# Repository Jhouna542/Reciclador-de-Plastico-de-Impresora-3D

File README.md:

# Reciclador-de-Plastico-de-Impresora-3D
El repositorio contiene los esquemas y PCB en KiCad, el código del microcontrolador ATxmega128A1U junto con su esqueleto y el informe del proyecto en formato PDF y en formato IEEE.

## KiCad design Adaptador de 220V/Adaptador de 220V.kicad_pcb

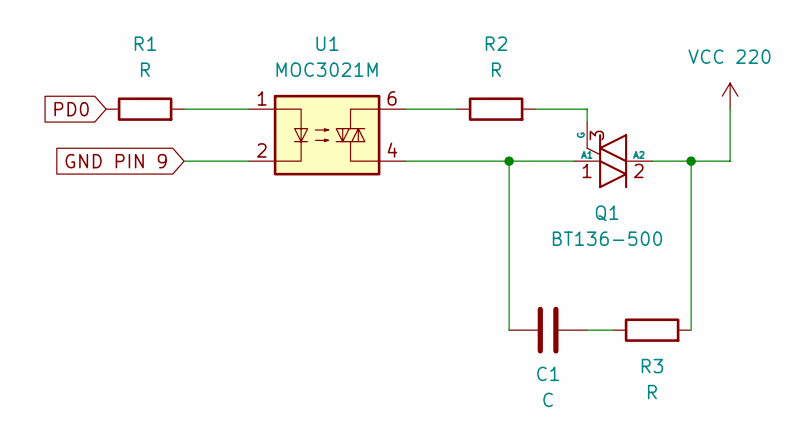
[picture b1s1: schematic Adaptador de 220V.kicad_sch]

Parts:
C1: C; C_Axial_L5.1mm_D3.1mm_P10.00mm_Horizontal
Q1: BT136-500; TO-220-3_Vertical
R1, R2, R3: R; R_Axial_DIN0207_L6.3mm_D2.5mm_P7.62mm_Horizontal
U1: MOC3021M; DIP-6_W7.62mm

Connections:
GND PIN 9: U1.2
unnamed: C1.2, R3.1
unnamed: C1.1, Q1.1 (A1), U1.4
unnamed: Q1.3 (G), R2.2
unnamed: R1.2, U1.1
unnamed: R2.1, U1.6
PD0: R1.1
VCC 220: Q1.2 (A2), R3.2

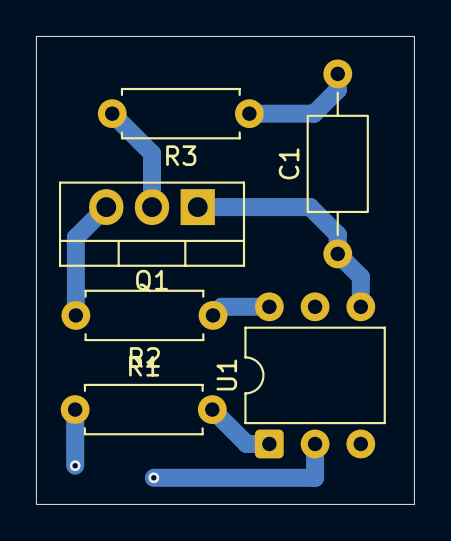
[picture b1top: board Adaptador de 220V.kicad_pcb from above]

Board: 2 copper layers, 21.0 x 26.0 mm, 6 parts (0 on the bottom side), 6 nets.

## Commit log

2025-11-28 README.md
